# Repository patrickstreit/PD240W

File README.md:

# PD240W

An adjustable power supply for motor drives using USB-C Power Delivery negotiation, supporting up to **240W at 48V 5A**. This device is designed to be compatible with USB-PD up to 3.2. Firmware runs on a Raspberry Pi Pico ([RP2040](https://www.raspberrypi.com/products/rp2040/)).

Follow the latest project logs and updates on <a href="https://hackaday.io/project/205084-pd240w" target="_blank" title="PD240W on Hackaday.io">
Hackaday.io 
</a>

> [!WARNING]
> **Disclaimer**: Firmware v2.0.0 includes guarded AVS/EPR negotiation, startup restore, and EPR-exit handling, but high-voltage charger interoperability still depends on the source and cable combination you test with. Validate 28V/36V/48V operation on your hardware.

## Table of Contents

- [Features](#features)
- [Hardware](#hardware)
- [Quick Start](#quick-start)
- [Controls](#controls)
- [Firmware Structure](#firmware-structure)
- [Want one?](#want-one)
- [Planned Features](#planned-features)
- [Acknowledgements](#acknowledgements)

## Features

- **USB-C Power Delivery**: Negotiates Fixed, PPS (3.3-21V programmable), and AVS (15-48V EPR) profiles
- **Current Limiting**: Adjustable 10mA-5A via INA228 power monitor with hardware overcurrent protection
- **LCD Interface**: 240x320 ST7789 display with anti-aliased fonts and Prusa-style encoder navigation
- **Safety**: Overcurrent ISR, overtemperature monitoring (NTC + INA228)
- **Settings Persistence**: User settings stored in RP2040 flash with CRC32 validation
- **Auto PPS/AVS Tuning**: Closed-loop voltage correction for PPS/AVS charger output accuracy
- **Charger Diagnostics**: On-device PD revision, charger identity, cable inference, and max-power reporting
- **Remote CLI**: USB serial command interface for measurements, PD selection, and settings updates
- **Energy Monitoring**: Tracks mAh delivered since boot via INA228 charge accumulator
- **17V Buck Output**: Optional mock STO/SBC voltage for motor drive safety circuits
- **Configurable**: Brightness, auto-dim, startup melody, auto-output on boot and more

## Hardware

| Type | Path | Contents |
|------|------|----------|
| PCB (STEP) | `3D_models/PD240W_PCB.stp` | Full PCB 3D model |
| Enclosure (STL) | `3D_models/enclosure/` | Casing top/bottom, knob, button, LCD support, SWD cover |
| Gerbers | `PCB_files/Manufacturing/Fabrication/` | PCB manufacturing files |
| BOM | `PCB_files/Manufacturing/Assembly/` | Bill of materials |
| Pick & Place | `PCB_files/Manufacturing/Assembly/` | Pick and place file |

### Hardware Erata

USB data lines (D+/D-) are reversed in the current PCB revision, preventing native USB communication between the RP2040 and the USB host. This can be easily fixed by crossing the D+ and D- lines on the PCB by crossing the series 27Ω resistors as shown below:

## Quick Start

### Flash Pre-built Firmware

1. Download `PD240W.uf2` from the [latest release](https://github.com/theohg/PD240W/releases/latest)
2. Hold **BOOTSEL** button on the Pico while connecting USB
3. Drag `PD240W.uf2` to the mounted `RPI-RP2` drive

### Build from Source

Requires: [Pico SDK 2.3.0](https://github.com/raspberrypi/pico-sdk), ARM GCC toolchain, CMake, Ninja

```bash
git clone --recurse-submodules https://github.com/theohg/PD240W.git
cd PD240W

mkdir -p build && cd build
cmake -G Ninja ..
ninja
```

The output binary is `build/PD240W.uf2`.

The INA228 driver is tracked as a Git submodule in `external/ina228_multiplatform`. If you already cloned the repository without submodules, run:

```bash
git submodule update --init --recursive
```

PD240W does not automatically follow the newest INA228 library release. The version is pinned by the parent repository's recorded submodule commit for `external/ina228_multiplatform`, and that exact checked-out commit is what gets compiled into the firmware. Prebuilt `PD240W.uf2` releases already include that pinned INA version.

### Flash via SWD

```bash
openocd -f interface/cmsis-dap.cfg -f target/rp2040.cfg \
  -c "adapter speed 5000; program build/PD240W.elf verify reset exit"
```

> [!IMPORTANT]
> **EEPROM Initial Setup**: Before full PD negotiation can work, you must flash the **TPS26750 EEPROM** configuration. This is done via the **EEPROM Flash** workflow found in the **Settings** menu. 
> 
> **Note**: Before the EEPROM is flashed, the board will only power on when connected to a standard 5V non-PD charger (USB BC1.2 mode).

Once the firmware has been successfully flashed, connect the device to a compatible USB-PD power source and interact with the encoder and buttons to navigate the menus and adjust settings as explained below.

> [!NOTE]
> Finding a compact and affordable charger supporting **USB-PD 3.1** (up to 48V EPR) is currently quite rare. Here are a few known options:
>
> | Model | Max single-port PD Output | Voltage Profile | Approx. Price |
> |---|---|---|---|
> | **[UGREEN Nexode 140W](https://fr.ugreen.com/products/ugreen-nexode-140w-chargeur-usb-c-pd-3-1-3-ports)** | 140W | 28V @ 5A | ~60€ |
> | **[Framework Power Adapter - 180W](https://frame.work/fr/fr/products/16-power-adapter?v=FRANCR000F)** | 180W | 36V @ 5A | ~109€ |
> | **[HKY 240W GaN Charger](https://www.amazon.de/-/en/Charger-Framework-Thunderbolt-External-ADP-240KB/dp/B0FLXY1HYW/ref=sr_1_2?crid=3N3IPHZQ5LLC7&dib=eyJ2IjoiMSJ9.Hby-yLg1Ti0JNivqvDzvN57zIH6zG4_c9wlyL50Z52GmOPyP_vKubcMJ3zNZ7RRcIgOo2FKgZio1hprqALfRdOTl2DQ7Dp27o4l66qmaDQw9ctSuX0EaWnDfyVwVAMaSwnUP7h1NBuraYlZnAgiljw.9cbe3P4mLf8D7-0faSCcJpKki5cfrjZLwFO-zW9XlJw&dib_tag=se&keywords=hky+240w&qid=1769454134&sprefix=hky+240w%2Caps%2C102&sr=8-2)** | 240W | 48V @ 5A | ~90€ |
> | **[Framework Power Adapter - 240W](https://frame.work/fr/fr/products/power-adapter-240w?v=FRAKMX000F)** | 240W | 48V @ 5A | ~120€ |
> | **[UGREEN NEXODE 500W](https://eu.ugreen.com/products/ugreen-nexode-500w-6-port-gan-desktop-fast-charger)** | 240W | 48V @ 5A | ~250€ |

## Controls

| Input | Action |
|-------|--------|
| Encoder Rotate | Navigate menus / Adjust values |
| Encoder Click | Confirm / Select |
| BTN1 (top) | Toggle load switch output |
| BTN2 (bottom) | Toggle 5V aux buck (requires VBUS > 7V) |

### Menu Structure

```mermaid
graph TD
  %% Nodes
      Boot([Boot]) -->|≤2s| Main[Main Screen]
      Main -->|Error| Fault[Fault Screen]
      Fault -->|Click| Main
      
      Main <-->|Click| Menu[Main Menu]

      Menu --> Voltage[Select Voltage]
      Menu --> Current[Current Limit]
      Menu --> Settings[Settings]
      Menu --> AboutFirmware[About PD240W]
      Menu --> AboutCharger[About This Charger]
      Menu --> Back[Back]

      Voltage <-->|Select PDO| AdjV[Adjust Voltage]
      Current <-->|Set Limit| AdjC[Adjust Current]
      
      Settings --> EEPROM[Flash EEPROM]
      Settings --> Configs[Params: Brightness / Sounds / Tuning...]
      AboutFirmware --> Main
      AboutCharger --> Main
      
      %% Styling
      classDef default fill:#f9f9f9,stroke:#333,stroke-width:1px;
      classDef alert fill:#ffcccc,stroke:#cc0000,stroke-width:2px;
      class Fault alert;
```

| Menu Item | Description |
|-----------|-------------|
| Select Voltage | Fixed / PPS / AVS PDO selection |
| Current Limit | 10mA - 5A output current limit adjustment with encoder acceleration |
| Settings | EEPROM flash workflow plus tuning, startup, brightness, and sound options |
| About PD240W | Device identity, firmware build info, flash usage, and project link |
| About This Charger | Live PD revision, CC orientation, QC inference, and cable diagnostics |
| Back | Return to the main live display |

## Firmware Structure

```
src/
├── main.cpp                        Entry point, non-blocking main event loop
├── hardware.h/cpp                  Hardware singleton aggregating all drivers
├── interrupts.h/cpp                Centralized GPIO interrupt router (RP2040 single-callback)
│
├── config/
│   ├── board_config.h              Pin definitions (Board:: namespace)
│   ├── app_config.h                Timeouts, thresholds, limits (AppConfig:: namespace)
│   └── version.h                   Firmware & hardware version, author...
│
├── drivers/                        Low-level hardware drivers (no business logic)
│   ├── display/
│   │   ├── st7789.h/cpp            SPI LCD driver with AA font rendering
│   │   ├── aa_font.h               Anti-aliased font data structure
│   │   └── font_inter_*.h          Generated Inter font bitmaps (14/20/28px)
│   ├── power/
│   │   └── tps26750/               USB-PD controller: PDO discovery, contract negotiation
│   ├── input/
│   │   ├── rotary_enc.h/cpp        Quadrature encoder with velocity tracking
│   │   ├── button.h/cpp            Debounced button with click/long-press
│   │   └── adc_inputs.h/cpp        VBUS voltage + NTC temperature (ADC channels)
│   ├── gpio/                       SimpleIO: digital output with non-blocking blink
│   ├── buzzer/                     PWM buzzer with melody playback
│   └── rgb_led/                    SK6812 via PIO state machine
│
├── logic/                          Application logic
│   ├── state_machine.h/cpp         BOOT -> MAIN <-> MENU <-> ADJUST, FAULT handling
│   ├── safety.h/cpp                Temperature/voltage/current monitoring, fault triggers
│   ├── pd_manager.h/cpp            PD contract caching, PPS keep-alive, auto-tuning
│   ├── settings.h/cpp              Flash persistence with CRC32, debounced saves
│   └── tps_eeprom_workflow.h/cpp   TPS26750 EEPROM compare/flash state machine
│
├── ui/
│   ├── display_manager.h/cpp       All screen rendering (boot, main, menu, adjust, fault)
│   ├── font_config.h               Central font size mapping (FONT_LARGE/MEDIUM/SMALL)
│   └── assets/synapticon_logo.h    Boot screen logo bitmap
│
├── utils/
│   ├── logging.h                   LOG_INFO/WARN/ERROR/DEBUG/CRITICAL macros
│   ├── pd_voltage.h                Shared programmable-voltage alignment helper
│   ├── tps_eeprom_loader.h/cpp     Low-level TPS26750 EEPROM read/write
│   └── tps26750_patch.c            TPS26750 binary configuration blob
```

## Want one?

Feel free to order assembled PCBs, flash the firmware, and test it for yourself! Manufacturing 5 assembled PCBs will cost approximately **$415**. 

The project is open for contributions. Don't hesitate to improve the code, report bugs, or suggest new features via Pull Requests and Issues!

## License and Copyright

This repository contains different types of source files, which are licensed as follows:

### 1. Hardware files (CC BY-NC 4.0)
All hardware design files in the PCB_files directory (Schematics, PCB layout, Gerbers, BOM) and 3D printable enclosure files are licensed under the **Creative Commons Attribution-NonCommercial 4.0 International License**. 

You are free to download, modify, and build this board for personal, educational, and hobbyist use. However, you may **not** use these designs for commercial purposes (such as manufacturing and selling the boards) without prior written permission.

Please see the [LICENSE.txt](./LICENSE.txt) file for full terms.

### 2. Firmware & Software (MIT License)
The firmware and software source code in this repository is licensed under the **MIT License**. 

You are free to use, modify, and distribute the software component of this project. 

Please see the [LICENSE-FIRMWARE.txt](./LICENSE-FIRMWARE.txt) file for full terms.

## Planned Features for V2.1.0+

- **PPS battery charging in Constant Current (CC) mode**: PPS allows a fixed current mode that can be used for battery charging. This is to be tested by charging lithium-ion battery packs.
- **Improved CLI interface**: Needs more testing and polish.
- **Extended PPS and AVS Range**: Support for PPS voltages as low as 3.5V, AND SPR AVS profiles down to 9V.

## Acknowledgements

This project was made possible by [Synapticon GmbH](https://www.synapticon.com), who funded and supported its development. Thank you for providing the resources, hardware, and opportunity to bring PD240W to life.

Inspiration for this project was taken from the great work on portable USB-C PD power supplies by CentyLab on the [PocketPD](https://hackaday.io/project/194295-pocketpd-usb-c-portable-bench-power-supply) project and Alex Xia with his [ProtoV MINI](https://hackaday.io/project/204461-protov-mini-tiny-usb-c-breadboard-power-supply).

All work done on this project, from Hardware design to Firmware development, was done by me, as the sole contributor. I am grateful for the support and feedback from the community, and I hope this project can be a useful resource for anyone interested in USB-C PD power supplies!

***

Made with ❤️ by Théo Heng

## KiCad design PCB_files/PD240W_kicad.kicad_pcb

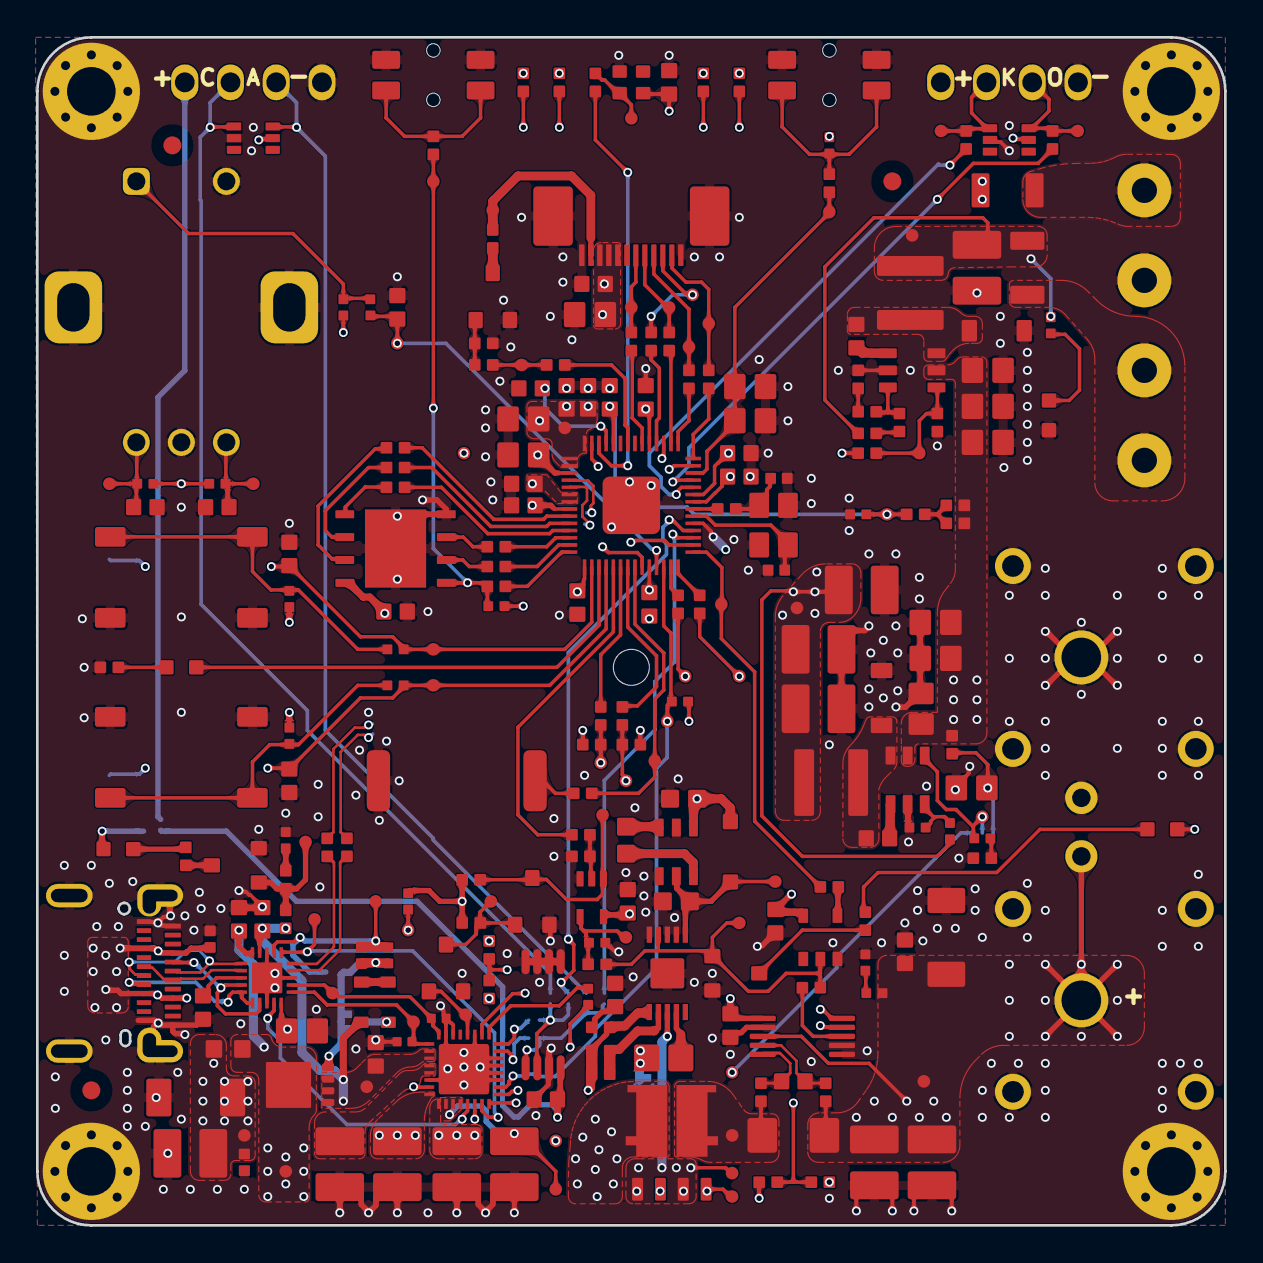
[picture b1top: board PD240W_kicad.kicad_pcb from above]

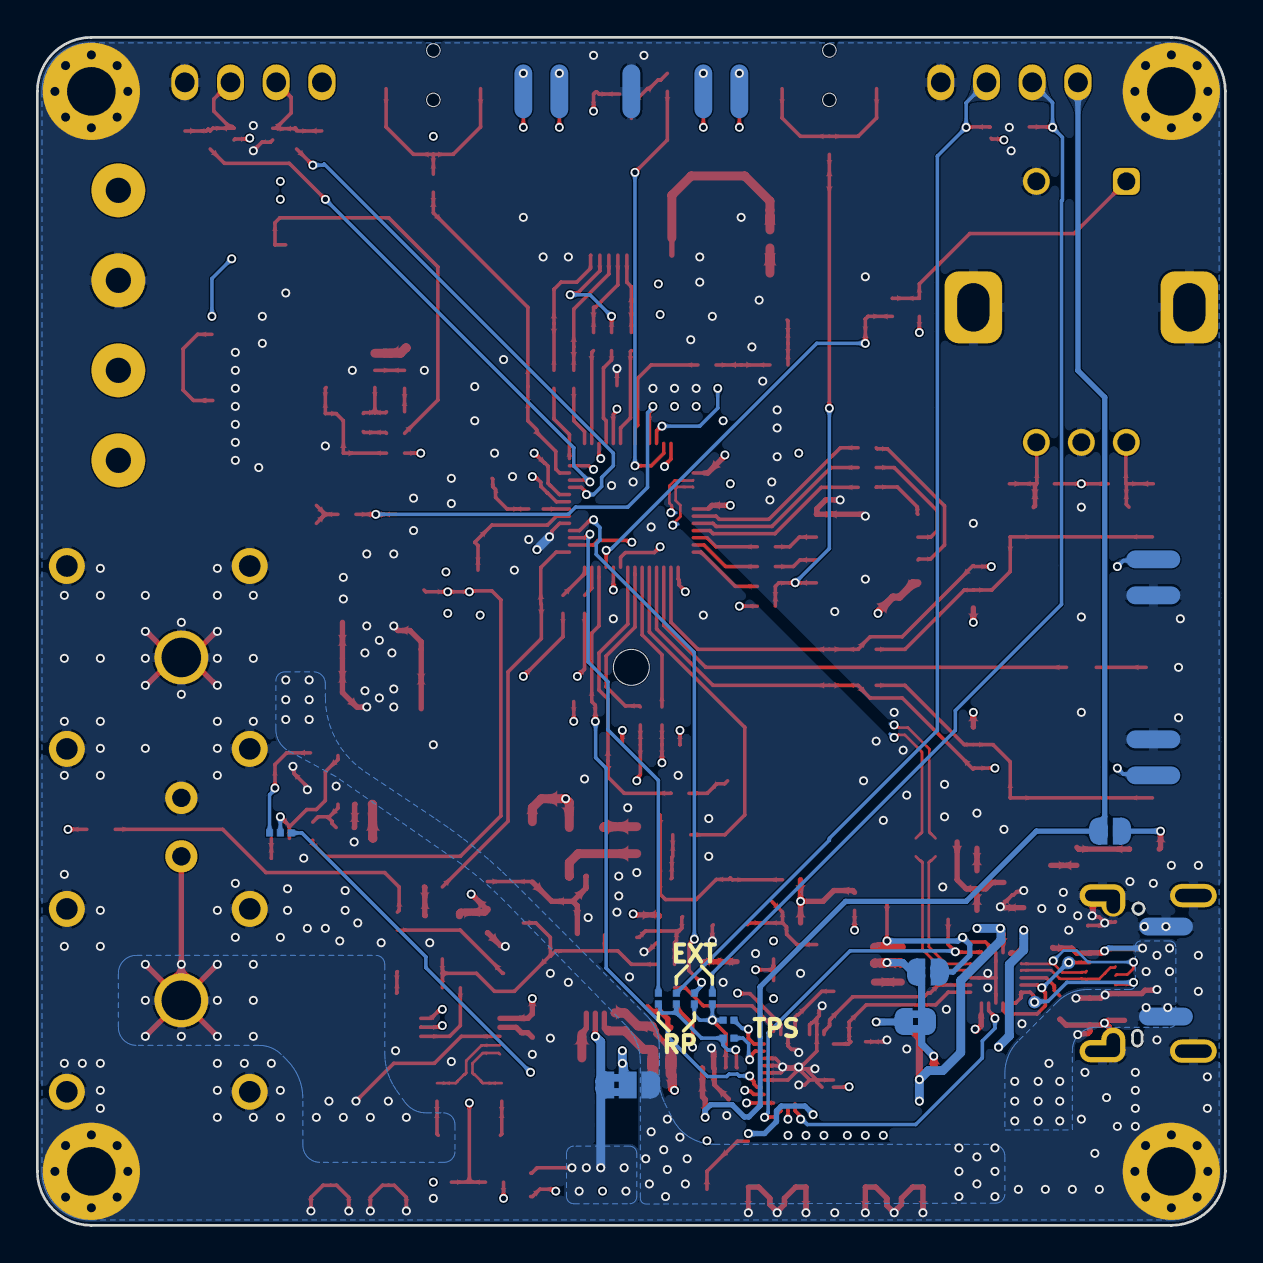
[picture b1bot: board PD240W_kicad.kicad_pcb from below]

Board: 6 copper layers, 66.0 x 66.0 mm, 299 parts (25 on the bottom side), 152 nets.

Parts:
C1, C2, C5: 10n X7R 100V; capc_1005_06_n
C3: 4.7u; capc_3225_22_n
C4, C6, C8, C16, C17, C21, C22, C23, C24, C25, C26, C27, C30, C34, C35, C37, C38, C39, C40, C41, C42, C43, C44, C47, C48, C49, C50, C52, C53, C54, C55, C63: 100n X7R 100V; capc_1608_09_l
C7, C31, C32, C33, C36, C51, C56, C57, C58, C62, C64, C65, C66: 1u X7R 100V; capc_2012_14_n
C9, C10, C11, C12, C28, C29, C59, C60, C61, C67: 10u X7R 63V; capc_3225_27_n
C13, C14, C15: 3.3u X5R 25V; capc_1608_09_n
C18: 2.2u X7R 100V; capc_2012_14_m
C19, C20: 220p X7R 50V; capc_1005_06_l
C45, C46: 15p COG 50V; capc_1005_06_n
D1, D8: SMAJ48A; do-214ac_440p_430x250x230_n_p
D2, D3: BZT52C18SQ; sod-323_230p_170x125x100_n
D4, D6, D9, D14: APTD1608LQBC/D; kingbright_0603_blue
D5: B0520LW-7-F; sod-123_270x155135_n
D7, D10: D3V3F4U6S-7; sot363_sc88_65p_200x125x110_n
D11: SK6812-EC20
D12, D13: MBR1H100SFT3G; sod-123fl_305p_260x160x90_n
DSP1: HS20HS072RX; generic_display_518x362x2_10mm_standoff
F1, F2: FSMD020-1206-R; ptc_1206_08_n
FB1: BLM18SN220TH1D; fer_1608_09_n
FD1, FD2, FD3: fiducial_generic; fiducial_round_130
J1: DX07S024JJ2R1300
J2, J7: 61300411121; we_61300411121
J3: 24.245.1; fcr7350r
J4: 24.245.2; fcr7350b
J5, J6: 1935776; phoenix_1935776
J8: AFC07-S12FCA-00
JP1: jumper_solder_2pad_nc_kicad; SolderJumper-2_P1.3mm_Bridged2Bar_RoundedPad1.0x1.5mm
JP2: jumper_solder_2pad_no; SolderJumper-2_P1.3mm_Open_RoundedPad1.0x1.5mm
JP3: jumper_solder_3pad_12nc_kicad; SolderJumper-3_P1.3mm_Bridged2Bar12_RoundedPad1.0x1.5mm
JP4, JP5, JP6, JP7, JP8, JP9: jumper_solder_2pad_no; jumper_solder_2pad_no_40x40_20
JP10: jumper_solder_2pad_no_kicad; SolderJumper-2_P1.3mm_Open_RoundedPad1.0x1.5mm
JP11: jumper_solder_3pad_no; jumper_solder_3pad_no_40x40_20
L1: 22uH 1A 0.29Ohm; SWPA4030S220MT
L2: 68uH 0.55A 0.91Ohm; SWPA4030S220MT
MH1: tooling_hole_200_0; tooling_hole_200_0_np
MH2, MH3, MH4, MH5: mounting_hole_270_540_p_via_8_50; MountingHole_2.7mm_M2.5_Pad_Via
NT1: nt_2pad_20x20_20_60x20; NetTie-2_SMD_Pad0.5mm
PZ1: FUET-9018; buzzer_9x9x2.1mm
Q1: AGM612AP; vsonp8_65p_330x330x80_mfg
Q2, Q4, Q5, Q6, Q7: AO3404A; sot-23-3L_103p_300x130x110_n
Q3: SQJB90EP-T1_GE3; PowerPAKSO-8_127p_513x615x120_n
R1, R3, R14, R15, R16, R17, R21, R27, R28, R29, R75, R81, R85: 100k 1%; resc_1005_04_m
R2, R4, R33, R34, R72, R78, R79, R80, R82: 33k 1%; resc_1005_04_n
R5, R35, R53, R54, R55, R63, R67: 1k 1%; resc_1005_04_m
R6, R10, R13, R19, R31, R36, R41, R69, R70, R71, R76, R77, R83: 10k 1%; resc_1005_04_n
R7, R23, R24, R26, R37, R38, R39, R40, R42, R43, R44, R45, R46, R47, R48, R49, R51, R52, R56, R57, R58, R59, R60, R61, R62, R64, R65, R66, R74: 27R 1%; resc_1005_04_m
R8, R9, R11, R12, R18, R25, R30, R84, R88, R89, R90: 4.7k 1%; resc_1005_04_m
R20, R50, R68: 330R 1%; resc_1005_04_m
R22: 8m 1%; WSLP1206_n_current_sense_6m_to_50m
R32: 10k @25°C; resc_1005_04_m
R73: 3.9R 1%; resc_1005_04_m
R86: 1k 1%; resc_1005_04_n
R87: 47k 1%; resc_1005_04_m
S1, S2: EVQ-PUC02K; EVQPUC02K
S3: PEC11R-4215F-S0024
S4, S5: GT-TC120A-H120-L1
TP1, TP2, TP46, TP47, TP48, TP49, TP50, TP51, TP52, TP53, TP54: sp_oval_300x100
TP3, TP4, TP5, TP6, TP7, TP8, TP9, TP10, TP11, TP12, TP13, TP14, TP15, TP16, TP17, TP18, TP19, TP20, TP21, TP22, TP23, TP24, TP25, TP26, TP27, TP28, TP29, TP30, TP33, TP34, TP35, TP36, TP37, TP38, TP39, TP40, TP41, TP42, TP43, TP44, TP45, TP55, TP56, TP57, TP58, TP59, TP60, TP61, TP62, TP63, TP64, TP65, TP66, TP67, TP68: tp_round_70
TP31, TP32: 5001
U1: TPD4S480RUKR; wqfn20_40p_300x300x80_tp_170x170_n
U2: LM2765; sot236_p95_290x160x110_n
U3: TPS26750SRSMR; qfn32_40p_400x400x100_tp_280x280_mfg
U4: LTC7004x; msop_10p_300x490x110_tp168x188_n
U5: 74LVC1G08SE-7; sot353_65p_200x125x110_mo-203-aa_n
U6: CAT24C512YI-GT3; JEDEC_MO-153_AA
U7: SN74LVC1G17DBVR; sot25_95p_300x280x145_jedec_mo-178-aa_n
U8: INA228AIDGSR; vssop10_50p_300x300x110_mfg
U9: RP2040; qfn56_40p_700x700x90_tp_320x320_mfg
U10: W25Q128JVPIQ; wson8_127p_600x500x80_tp_435x340_n
U11, U12: LMR16006XDDCR; sot6_p95_290x180x110_n
Y1: ABM8-272-T3; osccc_320x205x80_abm8

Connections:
+1V1: C33.1, C34.1, C35.1, TP33.1 (1_1), U9.23 (DVDD), U9.45 (VREG_VOUT), U9.50 (DVDD)
+1V5_LDO: C9.1, TP22.1 (1_1), U3.2 (ADCIN1), U3.3 (ADCIN2), U3.4 (LDO_1V5)
+3V3: C11.1, C24.1, C25.1, C36.1, C37.1, C38.1, C39.1, C40.1, C41.1, C42.1, C43.1, C44.1, C47.1, C51.1, C52.1, C59.1, C60.1, C61.1, D6.2 (A), D7.5, D10.5, D11.1 (VDD), F1.1, J7.1, J8.8, J8.9, J8.10, L1.2, R30.1, R36.1, R41.1, R69.1, R70.1, R71.1, R76.1, R77.1, R80.1, TP34.1 (1_1), TP65.1 (1_1), U3.32 (VIN_3V3), U7.5 (VCC), U8.6 (VS), U9.1 (IOVDD), U9.10 (IOVDD), U9.22 (IOVDD), U9.33 (IOVDD), U9.42 (IOVDD), U9.43 (ADC_AVDD), U9.44 (VREG_VIN), U9.48 (USB_VDD), U9.49 (IOVDD), U10.8 (VCC)
+3V3_EEPROM: C22.1, J2.1, JP10.1 (A), U6.8 (VCC)
+3V3_LDO: C7.1, C10.1, C13.1, C21.1, D4.2 (A), D5.2 (A), JP10.2 (B), R6.1, R8.1, R9.1, R10.1, R11.1, R12.1, R13.1, R15.1, R16.1, TP24.1 (1_1), U1.10 (VPWR), U2.1 (IN), U3.1 (LDO_3V3), U5.5 (VCC)
+6V6_LDO: C14.1, D5.1 (K), TP26.1 (1_1), U2.5 (OUT), U4.1 (VCC)
+17V: C67.1, F2.1, L2.2, R86.1, R87.1, TP64.1 (1_1)
+VBUS: C4.1, C56.1, C57.1, C58.1, C64.1, C65.1, C66.1, FB1.2, JP3.3 (B), Q1.3 (D), Q3.5 (D), R27.1, R28.1, R81.1, TP8.1 (1_1), U1.20 (VBUS), U11.5 (IN), U12.5 (IN)
+VBUS_LV: C6.1, C17.1, D3.1 (K), Q1.1 (S), R1.1, TP9.1 (1_1), U1.19 (VBUS_LV), U3.26 (VBUS), U3.27 (VBUS)
+VBUS_OUT: C28.1, C29.1, C30.1, D8.1 (A1), J3.1, R22.2, R24.1, R33.1, TP30.1 (1_1), TP31.1 (1_1), U8.8 (VBUS)
+VBUS_SENSED: Q3.6 (D), R22.1, R23.1, TP20.1 (1_1)
/Project Architecture/MCU - Unit/17V_EN: R59.2, R85.1, TP66.1 (1_1), U12.4 (~SHDN)
/Project Architecture/MCU - Unit/17V_EN_R: R59.1, U9.31 (GPIO20)
/Project Architecture/MCU - Unit/BUTTON_1: C53.1, R78.1, TP51.1 (1_1), TP57.1 (1_1), U9.2 (GPIO0)
/Project Architecture/MCU - Unit/BUTTON_2: C54.1, R79.1, TP52.1 (1_1), TP58.1 (1_1), U9.4 (GPIO2)
/Project Architecture/MCU - Unit/BUZZER_PWM_R: R68.1, TP56.1 (1_1), U9.8 (GPIO6)
/Project Architecture/MCU - Unit/ENCODER_A: C49.1, R69.2, S3.A, TP59.1 (1_1), U9.9 (GPIO7)
/Project Architecture/MCU - Unit/ENCODER_B: C50.1, R70.2, S3.B, TP60.1 (1_1), U9.16 (GPIO13)
/Project Architecture/MCU - Unit/ENCODER_BUTTON: C48.1, R72.2, TP61.1 (1_1), U9.11 (GPIO8)
/Project Architecture/MCU - Unit/GPIO14: R53.2, TP47.1 (1_1)
/Project Architecture/MCU - Unit/GPIO14_R: JP9.2 (B), R53.1, U9.17 (GPIO14)
/Project Architecture/MCU - Unit/GPIO15: R54.2, TP48.1 (1_1)
/Project Architecture/MCU - Unit/GPIO15_R: JP8.2 (B), R54.1, U9.18 (GPIO15)
/Project Architecture/MCU - Unit/GPIO16: R55.2, TP49.1 (1_1)
/Project Architecture/MCU - Unit/GPIO16_R: R55.1, U9.27 (GPIO16)
/Project Architecture/MCU - Unit/GPIO29: R67.2, TP50.1 (1_1)
/Project Architecture/MCU - Unit/GPIO29_R: R67.1, U9.41 (GPIO29/ADC3)
/Project Architecture/MCU - Unit/I2C0_SCL: R9.2, R49.2, TP40.1 (1_1), U3.9 (I2CT_SCL), U8.5 (SCL)
/Project Architecture/MCU - Unit/I2C0_SCL_R: R49.1, U9.7 (GPIO5)
/Project Architecture/MCU - Unit/I2C0_SDA: R8.2, R48.2, TP39.1 (1_1), U3.8 (I2CT_SDA), U8.4 (SDA)
/Project Architecture/MCU - Unit/I2C0_SDA_R: R48.1, U9.6 (GPIO4)
/Project Architecture/MCU - Unit/LCD_BACKLIGHT_EN: R65.2, R74.1, TP63.1 (1_1)
/Project Architecture/MCU - Unit/LCD_BACKLIGHT_EN_R: R65.1, U9.36 (GPIO24)
/Project Architecture/MCU - Unit/LCD_CS: J8.2, R56.2, TP41.1 (1_1)
/Project Architecture/MCU - Unit/LCD_CS_R: R56.1, U9.28 (GPIO17)
/Project Architecture/MCU - Unit/LCD_RS: J8.3, R60.2, TP45.1 (1_1)
/Project Architecture/MCU - Unit/LCD_RST: J8.6, R61.2, TP44.1 (1_1)
/Project Architecture/MCU - Unit/LCD_RST_R: R61.1, U9.34 (GPIO22)
/Project Architecture/MCU - Unit/LCD_RS_R: R60.1, U9.32 (GPIO21)
/Project Architecture/MCU - Unit/LCD_SCL: J8.4, R57.2, TP42.1 (1_1)
/Project Architecture/MCU - Unit/LCD_SCL_R: R57.1, U9.29 (GPIO18)
/Project Architecture/MCU - Unit/LCD_SDA: J8.5, R58.2, TP43.1 (1_1)
/Project Architecture/MCU - Unit/LCD_SDA_R: R58.1, U9.30 (GPIO19)
/Project Architecture/MCU - Unit/LED_DATA: D11.4 (DIN), R62.2, TP55.1 (1_1)
/Project Architecture/MCU - Unit/LED_DATA_R: R62.1, U9.40 (GPIO28/ADC2)
/Project Architecture/MCU - Unit/LED_DEBUG: D9.2 (A), U9.3 (GPIO1)
/Project Architecture/MCU - Unit/PD_GPIO1: R51.2, TP15.1 (1_1), U3.6 (GPIO1)
/Project Architecture/MCU - Unit/PD_GPIO1_R: R51.1, U9.13 (GPIO10)
/Project Architecture/MCU - Unit/PD_GPIO3: R52.2, TP18.1 (1_1), U3.18 (GPIO3)
/Project Architecture/MCU - Unit/PD_GPIO3_R: R52.1, U9.14 (GPIO11)
/Project Architecture/MCU - Unit/QSPI_SD0: R40.1, U10.5 (DI)
/Project Architecture/MCU - Unit/QSPI_SD0_R: R40.2, U9.53 (QSPI_SD0)
/Project Architecture/MCU - Unit/QSPI_SD1: R42.1, U10.2 (DO)
/Project Architecture/MCU - Unit/QSPI_SD1_R: R42.2, U9.55 (QSPI_SD1)
/Project Architecture/MCU - Unit/QSPI_SD2: R43.1, U10.3 (~WP)
/Project Architecture/MCU - Unit/QSPI_SD2_R: R43.2, U9.54 (QSPI_SD2)
/Project Architecture/MCU - Unit/QSPI_SD3: R44.1, U10.7 (~H/~R)
/Project Architecture/MCU - Unit/QSPI_SD3_R: R44.2, U9.51 (QSPI_SD3)
/Project Architecture/MCU - Unit/QSPI_SLCK: R45.1, U10.6 (CLK)
/Project Architecture/MCU - Unit/QSPI_SLCK_R: R45.2, U9.52 (QSPI_SCLK)
/Project Architecture/MCU - Unit/SWCLK: D10.1, J7.2, R64.1, TP35.1 (1_1)
/Project Architecture/MCU - Unit/SWCLK_R: R64.2, U9.24 (SWCLK)
/Project Architecture/MCU - Unit/SWDIO: D10.6, J7.3, R66.1, TP36.1 (1_1)
/Project Architecture/MCU - Unit/SWDIO_R: R66.2, U9.25 (SWDIO)
/Project Architecture/MCU - Unit/SWITCH_EN_MANUAL: R21.1, R47.2, U5.2 (B)
/Project Architecture/MCU - Unit/SWITCH_EN_MANUAL_R: R47.1, U9.5 (GPIO3)
/Project Architecture/MCU - Unit/SW_EN_READ: R25.2, TP29.1 (1_1), U9.15 (GPIO12)
/Project Architecture/MCU - Unit/TEMP_SENSE: C27.1, R30.2, R32.1, U9.39 (GPIO27/ADC1)
/Project Architecture/MCU - Unit/USB_D_INT_N: R39.2, U9.46 (USB_DM)
/Project Architecture/MCU - Unit/USB_D_INT_P: R38.2, U9.47 (USB_DP)
/Project Architecture/MCU - Unit/USB_D_N: R39.1, U1.14 (SBU2)
/Project Architecture/MCU - Unit/USB_D_P: R38.1, U1.15 (SBU1)
/Project Architecture/MCU - Unit/USB_PD_IRQ: R10.2, TP16.1 (1_1), U3.10 (*I2CT_IRQ), U9.12 (GPIO9)
/Project Architecture/MCU - Unit/V_SENSE: C26.1, R29.2, R31.1, TP27.1 (1_1), U9.38 (GPIO26/ADC0)
/Project Architecture/MCU - Unit/XIN: C46.1, U9.20 (XIN), Y1.1
/Project Architecture/MCU - Unit/XOUT: C45.1, R63.1, Y1.3
/Project Architecture/MCU - Unit/XOUT_R: R63.2, U9.21 (XOUT)
/Project Architecture/MCU - Unit/~BOOT: R35.2, S1.1, S1.3
/Project Architecture/MCU - Unit/~QSPI_SS_R: R46.2, U9.56 (QSPI_SS_N)
/Project Architecture/MCU - Unit/~QSPI_SS: R35.1, R41.2, R46.1, TP38.1 (1_1), U10.1 (~CS)
/Project Architecture/MCU - Unit/~RESET: C31.1, C32.1, R37.1, TP37.1 (1_1), U9.26 (RUN)
/Project Architecture/MCU - Unit/~RST: R36.2, R37.2, S2.1, S2.3
/Project Architecture/Power - Generation/3V3_CB: C55.1, U11.1 (CB)
/Project Architecture/Power - Generation/3V3_EN: JP11.2 (C), R82.1, TP67.1 (1_1), U11.4 (~SHDN)
/Project Architecture/Power - Generation/3V3_EN_PD: JP11.1 (A), TP68.1 (1_1), U3.31 (GPIO6)
/Project Architecture/Power - Generation/3V3_FB: R80.2, R83.1, U11.3 (FB)
/Project Architecture/Power - Generation/3V3_SW: C55.2, D12.1 (K), L1.1, U11.6 (SW)
/Project Architecture/Power - Generation/17V_CB: C63.1, U12.1 (CB)
/Project Architecture/Power - Generation/17V_FB: R88.2, R89.1, U12.3 (FB)
/Project Architecture/Power - Generation/17V_SW: C63.2, D13.1 (K), L2.1, U12.6 (SW)
/Project Architecture/Power - Generation/LED_17V_A: D14.2 (A), R86.2
/Project Architecture/Power - Output/3V3_FUSED: F1.2, J5.1
/Project Architecture/Power - Output/17V_FUSED: F2.2, J6.1, J6.2
/Project Architecture/Power - PD Controller/CAP+: C15.1, U2.6 (CAP+)
/Project Architecture/Power - PD Controller/CAP-: C15.2, U2.3 (CAP-)
/Project Architecture/Power - PD Controller/CC1: C20.1, TP3.1 (1_1), U1.12 (CC1), U3.24 (CC1)
/Project Architecture/Power - PD Controller/CC2: C19.1, TP5.1 (1_1), U1.11 (CC2), U3.25 (CC2)
/Project Architecture/Power - PD Controller/EPR_EN: TP11.1 (1_1), U1.16 (EPR_EN), U3.7 (GPIO2)
/Project Architecture/Power - PD Controller/I2CC_IRQ: R13.2, U3.17 (*I2CC_IRQ)
/Project Architecture/Power - PD Controller/I2CC_SCL: JP6.2 (B), U3.16 (I2CC_SCL)
/Project Architecture/Power - PD Controller/I2CC_SCL_EEPROM: JP6.1 (A), JP7.2 (B), JP8.1 (A), R12.2, U6.6 (SCL)
/Project Architecture/Power - PD Controller/I2CC_SCL_EXT: D7.1, J2.2, JP7.1 (A)
/Project Architecture/Power - PD Controller/I2CC_SDA: JP4.2 (B), U3.15 (I2CC_SDA)
/Project Architecture/Power - PD Controller/I2CC_SDA_EEPROM: JP4.1 (A), JP5.2 (B), JP9.1 (A), R11.2, U6.5 (SDA)
/Project Architecture/Power - PD Controller/I2CC_SDA_EXT: D7.6, J2.3, JP5.1 (A)
/Project Architecture/Power - PD Controller/LTC_BST: C18.2, U4.9 (BST)
/Project Architecture/Power - PD Controller/LTC_GATE: Q3.2 (G), Q3.4 (G), R7.2, R14.2, R17.2, TP25.1 (1_1), U4.6 (TGDN)
/Project Architecture/Power - PD Controller/POWER_PATH_EN: Q4.1 (G), TP14.1 (1_1), U3.20 (POWER_PATH_EN)
/Project Architecture/Power - PD Controller/PP5V: C12.1, U3.28 (PP5V), U3.29 (PP5V)
/Project Architecture/Power - PD Controller/PP_EN1: Q4.3 (D), Q5.1 (G), R15.2, TP17.1 (1_1)
/Project Architecture/Power - PD Controller/PP_EN2: Q5.3 (D), R16.2, TP19.1 (1_1), U5.1 (A)
/Project Architecture/Power - PD Controller/PP_EN3: R18.1, R19.1, TP21.1 (1_1), U5.4 (Y)
/Project Architecture/Power - PD Controller/SWITCH_EN: Q6.1 (G), R18.2, R26.2, TP28.1 (1_1), U4.4 (INP), U7.2 (A)
/Project Architecture/Power - PD Controller/TS: C18.1, JP3.1 (A), JP3.2 (C), Q3.1 (S), Q3.3 (S), TP23.1 (1_1), U4.8 (TS)
/Project Architecture/Power - PD Controller/~FLT: R6.2, TP12.1 (1_1), U1.9 (~FLT), U3.5 (GPIO0)
/Project Architecture/Power - Sensing/INA_ALERT: R26.1, U8.3 (ALERT)
/Project Architecture/Power - Sensing/SENSE_N: C23.2, R24.2, U8.9 (IN-)
/Project Architecture/Power - Sensing/SENSE_P: C23.1, R23.2, U8.10 (IN+)
/Project Architecture/Power - USB-C Input/+VBUS_C: C1.1, C2.1, C3.1, D1.1 (A1), FB1.1, J1.A4, J1.A9, J1.B4, J1.B9, TP1.1 (1_1), TP7.1 (1_1)
/Project Architecture/Power - USB-C Input/+VBUS_LV/2: Q2.1 (G), R1.2, R3.1, TP13.1 (1_1)
/Project Architecture/Power - USB-C Input/CC1_C: J1.A5, TP4.1 (1_1), U1.4 (C_CC1), U1.7 (RPD_G1)
/Project Architecture/Power - USB-C Input/CC2_C: J1.B5, TP6.1 (1_1), U1.5 (C_CC2), U1.6 (RPD_G2)
/Project Architecture/Power - USB-C Input/EPR_BLK_G: C5.2, JP2.1 (A), R2.2, TP10.1 (1_1), U1.17 (EPR_BLK_G)
/Project Architecture/Power - USB-C Input/LED_IN_D: Q2.3 (D), R5.2
/Project Architecture/Power - USB-C Input/LED_IN_K: D4.1 (C), R5.1
/Project Architecture/Power - USB-C Input/USB_D_C_N: J1.A7, J1.B7, U1.2 (C_SBU2)
/Project Architecture/Power - USB-C Input/USB_D_C_P: J1.A6, J1.B6, U1.1 (C_SBU1)
/Project Architecture/Power - USB-C Input/VBIAS: C8.1, U1.3 (VBIAS)
/Project Architecture/Power - USB-C Input/VBUS_LV_GATE: C5.1, D2.1 (K), JP1.1 (A), JP1.2 (B), JP2.2 (B), Q1.2 (G), R2.1
/Project Architecture/User - Interface/BUZZER_PWM: PZ1.1 (+), R68.2
/Project Architecture/User - Interface/LCD_BACKLIGHT: J8.11, R73.1, TP62.1 (1_1)
/Project Architecture/User - Interface/LCD_DRAIN: Q7.3 (D), R73.2
/Project Architecture/User - Interface/LCD_GATE: Q7.1 (G), R74.2, R75.1
GND: C1.2, C2.2, C3.2, C4.2, C6.2, C7.2, C8.2, C9.2, C10.2, C11.2, C12.2, C13.2, C14.2, C16.2, C17.2, C19.2, C20.2, C21.2, C22.2, C24.2, C25.2, C26.2, C27.2, C28.2, C29.2, C30.2, C31.2, C32.2, C33.2, C34.2, C35.2, C36.2, C37.2, C38.2, C39.2, C40.2, C41.2, C42.2, C43.2, C44.2, C45.2, C46.2, C47.2, C48.2, C49.2, C50.2, C51.2, C52.2, C53.2, C54.2, C56.2, C57.2, C58.2, C59.2, C60.2, C61.2, C62.2, C64.2, C65.2, C66.2, C67.2, D1.2 (A2), D7.2, D8.2 (A2), D10.2, D11.3 (VSS), D12.2 (A), D13.2 (A), D14.1 (C), J1.A1, J1.A12, J1.B1, J1.B12, J1.MP1 (MP), J1.MP2 (MP), J1.MP3 (MP), J1.MP4 (MP), J2.4, J3.MP1 (MP), J3.MP2 (MP), J3.MP3 (MP), J3.MP4 (MP), J4.1, J4.MP1 (MP), J4.MP2 (MP), J4.MP3 (MP), J4.MP4 (MP), J5.2, J7.4, J8.1, J8.12, J8.MP1 (MP), J8.MP2 (MP), MH2.1 (1_1), MH3.1 (1_1), MH4.1 (1_1), MH5.1 (1_1), NT1.2, PZ1.2 (-), Q2.2 (S), Q4.2 (S), Q5.2 (S), Q6.2 (S), Q7.2 (S), R4.2, R19.2, R21.2, R31.2, R34.2, R50.2, R75.2, R83.2, R84.2, R85.2, R90.2, S1.2, S1.4, S2.2, S2.4, S3.2, S3.C, S3.MP1, S3.MP2, S4.3, S4.4, S5.3, S5.4, TP2.1 (1_1), TP32.1 (1_1), TP46.1 (1_1), TP53.1 (1_1), TP54.1 (1_1), U1.8 (GND), U1.13 (GND), U1.18 (GND), U1.21 (EP), U2.2 (GND), U2.4 (SD), U3.11 (GND), U3.12 (GND), U3.13 (GPIO11), U3.14 (GND), U3.19 (GND), U3.22 (GPIO4/USB_P/LD1), U3.23 (GPIO5/USB_N/LD2), U3.30 (GPIO7), U3.33 (GND), U4.2 (VCCUV), U4.3 (GND), U4.5 (OVLO), U4.11 (GND), U5.3 (GND), U6.1 (A0), U6.2 (A1), U6.3 (A2), U6.4 (VSS), U6.7 (WP), U7.3 (GND), U8.1 (A1), U8.2 (A0), U8.7 (GND), U9.19 (TESTEN), U9.57 (GND), U10.4 (GND), U10.9 (EP), U11.2 (GND), U12.2 (GND), Y1.2, Y1.4
unnamed: C16.1, R7.1
unnamed: D2.2 (A), D3.2 (A)
unnamed: D6.1 (C), R20.1
unnamed: D9.1 (C), R50.1
unnamed: C62.1, JP11.3 (B), R81.2
unnamed: NT1.1, R32.2
unnamed: Q6.3 (D), R20.2
unnamed: R3.2, R4.1
unnamed: R27.2, R28.2, R29.1
unnamed: R33.2, R34.1
unnamed: R71.2, R72.1, S3.1
unnamed: R76.2, R78.2, S4.1, S4.2
unnamed: R77.2, R79.2, S5.1, S5.2
unnamed: R82.2, R84.1
unnamed: R87.2, R88.1
unnamed: R89.2, R90.1
unnamed: R14.1, R17.1, U4.7 (TGUP)
unnamed: R25.1, U7.4 (Y)

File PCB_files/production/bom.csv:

Designator,Footprint,Quantity,Value,LCSC Part #
"C1, C2, C5",capc_1005_06_n,3,10n X7R 100V,C527014
"C10, C11, C12, C28, C29, C59, C60, C61, C67, C9",capc_3225_27_n,10,10u X7R 63V,C437568
"C13, C14, C15",capc_1608_09_n,3,3.3u X5R 25V,C5360803
"C16, C17, C21, C22, C23, C24, C25, C26, C27, C30, C34, C35, C37, C38, C39, C4, C40, C41, C42, C43, C44, C47, C48, C49, C50, C52, C53, C54, C55, C6, C63, C8",capc_1608_09_l,32,100n X7R 100V,C15725
C18,capc_2012_14_m,1,2.2u X7R 100V,C22367838
"C19, C20",capc_1005_06_l,2,220p X7R 50V,C296710
C3,capc_3225_22_n,1,4.7u,C913445
"C31, C32, C33, C36, C51, C56, C57, C58, C62, C64, C65, C66, C7",capc_2012_14_n,13,1u X7R 100V,C5370002
"C45, C46",capc_1005_06_n,2,15p COG 50V,C1548
"D1, D8",do-214ac_440p_430x250x230_n_p,2,SMAJ48A,C41376401
"D10, D7",sot363_sc88_65p_200x125x110_n,2,D3V3F4U6S-7,C1869321
D11,SK6812-EC20,1,SK6812-EC20,C2909058
"D12, D13",sod-123fl_305p_260x160x90_n,2,MBR1H100SFT3G,C235757
"D14, D4, D6, D9",kingbright_0603_blue,4,APTD1608LQBC/D,C5344742
"D2, D3",sod-323_230p_170x125x100_n,2,BZT52C18SQ,C2857090
D5,sod-123_270x155135_n,1,B0520LW-7-F,C155367
DSP1,generic_display_518x362x2_10mm_standoff,1,HS20HS072RX,C5329582
"F1, F2",ptc_1206_08_n,2,FSMD020-1206-R,C220145
FB1,fer_1608_09_n,1,BLM18SN220TH1D,C710392
J1,DX07S024JJ2R1300,1,DX07S024JJ2R1300,C2977282
J3,fcr7350r,1,24.245.1,C7437326
J4,fcr7350b,1,24.245.2,C7437327
"J5, J6",phoenix_1935776,2,1935776,C3817389
J8,AFC07-S12FCA-00,1,AFC07-S12FCA-00,C262559
L1,SWPA4030S220MT,1,22uH 1A 0.29Ohm,C83472
L2,SWPA4030S220MT,1,68uH 0.55A 0.91Ohm,C340217
PZ1,buzzer_9x9x2.1mm,1,FUET-9018,C391035
Q1,vsonp8_65p_330x330x80_mfg,1,AGM612AP,C5349119
"Q2, Q4, Q5, Q6, Q7",sot-23-3L_103p_300x130x110_n,5,AO3404A,C30010
Q3,PowerPAKSO-8_127p_513x615x120_n,1,SQJB90EP-T1_GE3,C727731
"R1, R14, R15, R16, R17, R21, R27, R28, R29, R3, R75, R81, R85, R87, R88",resc_1005_04_m,15,100k 1%,C25741
"R10, R13, R19, R31, R36, R41, R6, R69, R70, R71, R76, R77, R83, R86",resc_1005_04_n,14,10k 1%,C25744
"R11, R12, R18, R25, R30, R8, R84, R89, R9, R90",resc_1005_04_m,10,4.7k 1%,C25900
"R2, R33, R34, R4, R72, R78, R79, R80, R82",resc_1005_04_n,9,33k 1%,C138003
"R20, R50, R68",resc_1005_04_m,3,330R 1%,C25104
R22,WSLP1206_n_current_sense_6m_to_50m,1,8m 1%,C2988654
"R23, R24, R26, R37, R38, R39, R40, R42, R43, R44, R45, R46, R47, R48, R49, R51, R52, R56, R57, R58, R59, R60, R61, R62, R64, R65, R66, R7, R74",resc_1005_04_m,29,27R 1%,C138021
R32,resc_1005_04_m,1,10k @25°C,C95939
"R35, R5, R53, R54, R55, R63, R67",resc_1005_04_m,7,1k 1%,C11702
R73,resc_1005_04_m,1,3.9R 1%,C2933095
"S1, S2",EVQPUC02K,2,EVQ-PUC02K,C79174
S3,PEC11R-4215F-S0024,1,PEC11R-4215F-S0024,C143790
"S4, S5",GT-TC120A-H120-L1,2,GT-TC120A-H120-L1,C2762973
U1,wqfn20_40p_300x300x80_tp_170x170_n,1,TPD4S480RUKR,C43131250
U10,wson8_127p_600x500x80_tp_435x340_n,1,W25Q128JVPIQ,C190862
"U11, U12",sot6_p95_290x180x110_n,2,LMR16006XDDCR,C87080
U2,sot236_p95_290x160x110_n,1,LM2765,C140270
U3,qfn32_40p_400x400x100_tp_280x280_mfg,1,TPS26750SRSMR,C42166327
U4,msop_10p_300x490x110_tp168x188_n,1,LTC7004x,C690106
U5,sot353_65p_200x125x110_mo-203-aa_n,1,74LVC1G08SE-7,C460522
U6,JEDEC_MO-153_AA,1,CAT24C512YI-GT3,C56096
U7,sot25_95p_300x280x145_jedec_mo-178-aa_n,1,SN74LVC1G17DBVR,C7836
U8,vssop10_50p_300x300x110_mfg,1,INA228AIDGSR,C2887910
U9,qfn56_40p_700x700x90_tp_320x320_mfg,1,RP2040,C2040
Y1,osccc_320x205x80_abm8,1,ABM8-272-T3,C20625731
